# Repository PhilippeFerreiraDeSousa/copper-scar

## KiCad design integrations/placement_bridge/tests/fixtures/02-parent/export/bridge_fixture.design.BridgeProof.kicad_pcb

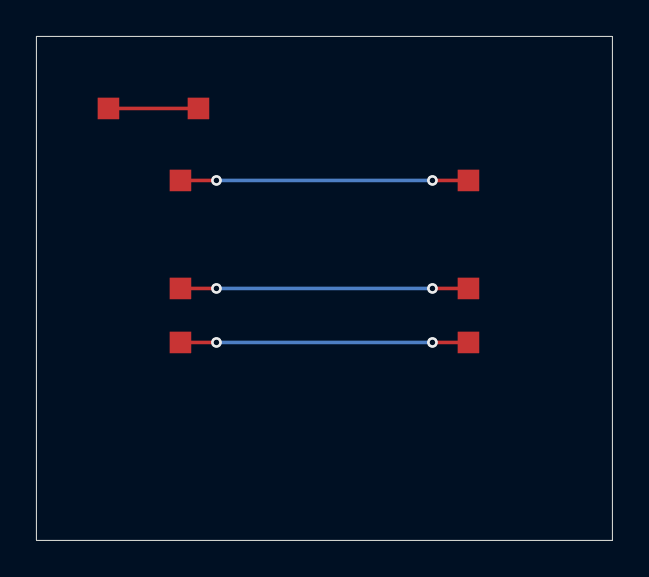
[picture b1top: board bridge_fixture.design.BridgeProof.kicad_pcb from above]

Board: 2 copper layers, 32.0 x 28.0 mm, 8 parts (0 on the bottom side), 4 nets.

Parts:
TP1, TP2, TP3, TP4, TP5, TP6, TP7, TP8: TESTLANDPATTERN

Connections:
CROSS_A: TP3.p, TP4.p
CROSS_B: TP5.p, TP6.p
CROSS_C: TP7.p, TP8.p
HOLD: TP1.p, TP2.p

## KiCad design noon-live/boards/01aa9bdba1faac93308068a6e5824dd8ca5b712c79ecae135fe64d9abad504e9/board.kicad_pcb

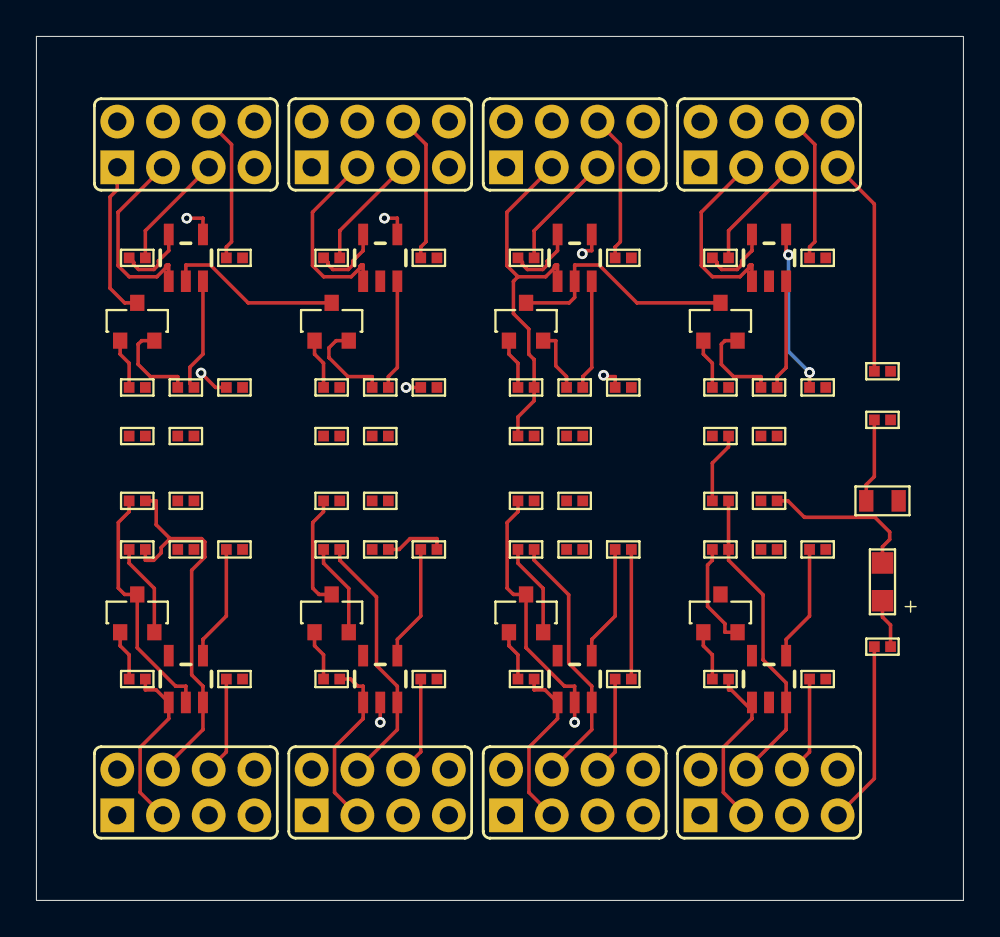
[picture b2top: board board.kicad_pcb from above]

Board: 4 copper layers, 51.5 x 48.0 mm, 85 parts (0 on the bottom side), 67 nets.

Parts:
C5, C46: 100nF; 0402-C
C50: 10u; 0805-C
J101, J102, J103, J104, J105, J106, J107, J108: HEADER_2x04_2.54mm_POPULATED; 2X04
LED6: CH1_PWR; CHIPLED
LED10, LED11, LED12, LED13, LED14, LED15, LED16, LED17: LED-CC-GREEN-RED-AM23ESG; SOT23-3
Q2, Q3, Q4, Q5, Q6, Q7, Q8, Q9: NFET-DUAL-COMMON-SOURCE-QS5K2; SOT23-5
R13, R14, R15, R16, R17, R18, R19, R20: 100k; 0402-R
R74: 3k3; 0402-R
R78, R79, R80, R81, R98, R99, R100, R101, R102, R103, R104, R105, R122, R123, R124, R125: 10k; 0402-R
R82, R83, R84, R85, R86, R87, R88, R89, R91, R93, R95, R97, R106, R107, R108, R109, R110, R111, R112, R113, R115, R117, R119, R121: 100; 0402-R
R90, R92, R94, R96, R114, R116, R118, R120: 1k; 0402-R

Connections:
CH1_SBU1: J101.5, R19.2, R90.2, R91.2
CH1_SBU1_IGN: J101.3, Q2.1 (G1), R78.1, R83.2
CH1_SBU1_RELAY: J101.4, Q2.3 (G2), R82.2, R98.2
CH1_SBU2: J105.5, R20.2, R114.2, R115.2
CH1_SBU2_IGN: J105.3, Q6.1 (G1), R102.1, R107.2
CH1_SBU2_RELAY: J105.4, Q6.3 (G2), R106.2, R122.2
CH2_SBU1: J102.5, R15.2, R92.2, R93.2
CH2_SBU1_IGN: J102.3, Q3.1 (G1), R79.1, R85.2
CH2_SBU1_RELAY: J102.4, Q3.3 (G2), R84.2, R99.2
CH2_SBU2: J106.5, R13.2, R116.2, R117.2
CH2_SBU2_IGN: J106.3, Q7.1 (G1), R103.1, R109.2
CH2_SBU2_RELAY: J106.4, Q7.3 (G2), R108.2, R123.2
CH3_SBU1: J103.5, R17.2, R94.2, R95.2
CH3_SBU1_IGN: J103.3, Q4.1 (G1), R80.1, R87.2
CH3_SBU1_RELAY: J103.4, Q4.3 (G2), R86.2, R100.2
CH3_SBU2: J107.5, R18.2, R118.2, R119.2
CH3_SBU2_IGN: J107.3, Q8.1 (G1), R104.1, R111.2
CH3_SBU2_RELAY: J107.4, Q8.3 (G2), R110.2, R124.2
CH4_SBU1: J104.5, R16.2, R96.2, R97.2
CH4_SBU1_IGN: J104.3, Q5.1 (G1), R81.1, R89.2
CH4_SBU1_RELAY: J104.4, Q5.3 (G2), R88.2, R101.2
CH4_SBU2: J108.5, R14.2, R120.2, R121.2
CH4_SBU2_IGN: J108.3, Q9.1 (G1), R105.1, R113.2
CH4_SBU2_RELAY: J108.4, Q9.3 (G2), R112.2, R125.2
EXT_5V: C5.1, C46.1, C50.1, J101.2, J101.7, J102.2, J102.7, J103.2, J103.7, J104.2, J104.7, J105.2, J105.7, J106.2, J106.7, J107.2, J107.7, J108.2, J108.7, R74.1
GND: C5.2, C46.2, C50.2, J101.1, J101.8, J102.1, J102.8, J103.1, J103.8, J104.1, J104.8, J105.1, J105.8, J106.1, J106.8, J107.1, J107.8, J108.1, J108.8, LED6.C, LED10.3 (C), LED11.3 (C), LED12.3 (C), LED13.3 (C), LED14.3 (C), LED15.3 (C), LED16.3 (C), LED17.3 (C), Q2.2 (S), Q3.2 (S), Q4.2 (S), Q5.2 (S), Q6.2 (S), Q7.2 (S), Q8.2 (S), Q9.2 (S), R78.2, R79.2, R80.2, R81.2, R98.1, R99.1, R100.1, R101.1, R102.2, R103.2, R104.2, R105.2, R122.1, R123.1, R124.1, R125.1
unnamed: LED6.A, R74.2
unnamed: LED10.2 (AG), R82.1
unnamed: LED10.1 (AR), R83.1
unnamed: LED11.2 (AG), R84.1
unnamed: LED11.1 (AR), R85.1
unnamed: LED12.2 (AG), R86.1
unnamed: LED12.1 (AR), R87.1
unnamed: LED13.2 (AG), R88.1
unnamed: LED13.1 (AR), R89.1
unnamed: LED14.2 (AG), R106.1
unnamed: LED14.1 (AR), R107.1
unnamed: LED15.2 (AG), R108.1
unnamed: LED15.1 (AR), R109.1
unnamed: LED16.2 (AG), R110.1
unnamed: LED16.1 (AR), R111.1
unnamed: LED17.2 (AG), R112.1
unnamed: LED17.1 (AR), R113.1
unnamed: Q2.5 (D1), R90.1
unnamed: Q2.4 (D2), R91.1
unnamed: Q3.5 (D1), R92.1
unnamed: Q3.4 (D2), R93.1
unnamed: Q4.5 (D1), R94.1
unnamed: Q4.4 (D2), R95.1
unnamed: Q5.5 (D1), R96.1
unnamed: Q5.4 (D2), R97.1
unnamed: Q6.5 (D1), R114.1
unnamed: Q6.4 (D2), R115.1
unnamed: Q7.5 (D1), R116.1
unnamed: Q7.4 (D2), R117.1
unnamed: Q8.5 (D1), R118.1
unnamed: Q8.4 (D2), R119.1
unnamed: Q9.5 (D1), R120.1
unnamed: Q9.4 (D2), R121.1
unnamed: J103.6, R17.1
unnamed: J107.6, R18.1
unnamed: J101.6, R19.1
unnamed: J105.6, R20.1
unnamed: J106.6, R13.1
unnamed: J108.6, R14.1
unnamed: J102.6, R15.1
unnamed: J104.6, R16.1
